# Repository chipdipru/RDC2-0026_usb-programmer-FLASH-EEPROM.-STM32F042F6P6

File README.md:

<p>USB-программатор предназначен для записи и чтения микросхем памяти серий 24хх, 25хх, 93хх, 95хх. На плате установлена панель для микросхем в корпусе DIP-8, предусмотрены посадочные места для микросхем в корпусах SOIC-8 и SOIC-16 (для серии 25хх). Все необходимые для работы с микросхемами сигналы выведены на разъемы.<br>
Для записи микросхем памяти необходимы файлы формата .bin. Программатор автоматически конвертирует файлы E2Prom.Hex SigmaStudio в .bin для записи.</p>
<p>Характеристики<br>
поддерживаемые серии микросхем памяти: 24хх, 25хх, 93хх, 95хх<br>
поддерживаемые корпуса: DIP-8, SOIC-8, SOIC-16 (для серии 25хх)<br>
максимальная тактовая частота: 24хх – 1 МГц; 25хх / 95хх – 24 МГц; 93хх – 2 МГц<br>
напряжение питания микросхем памяти: 3,3 В<br>
формат файла для записи / чтения: .bin, SigmaStudio .hex<br>
чтение / запись регистра состояния микросхем памяти<br>
хранение шаблонов микросхем памяти в формате .txt</p>

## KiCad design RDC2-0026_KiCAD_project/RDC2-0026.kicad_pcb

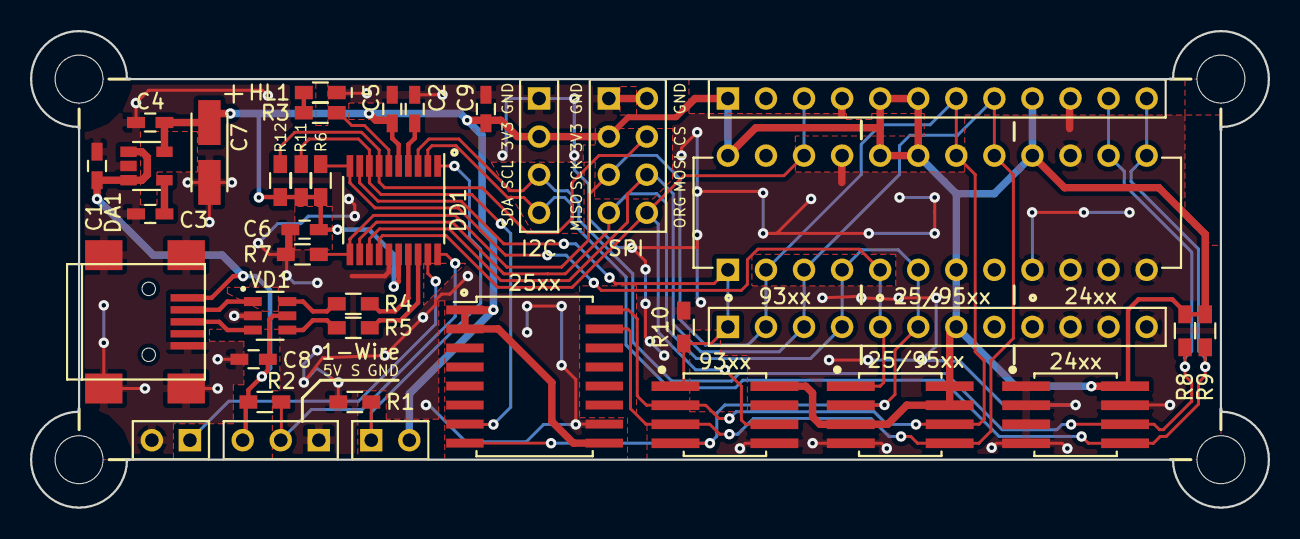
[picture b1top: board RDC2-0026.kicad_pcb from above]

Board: 2 copper layers, 82.6 x 31.8 mm, 38 parts (0 on the bottom side), 26 nets.

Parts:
24xx: 24XX EEPROM; SOIC-8_combo_Pitch1.27mm
25/95xx: 25LC_EEPROM; SOIC-8_combo_Pitch1.27mm
25xx: 25xx_spi_flash; SOIC-16_7.5x10.3mm_Pitch1.27mm_long_pads
93xx: 93LCxxC; SOIC-8_combo_Pitch1.27mm
C1, C4: 4,7мкФ; C_0603_HandSoldering
C2, C5, C6, C8, C9: 0,1мкФ; C_0603_HandSoldering
C3: 0,01мкФ; C_0603_HandSoldering
C7: 10мкФ; TantalC_SizeA_EIA-3216_HandSoldering_mm
DA1: LP2985AIM5-3.3; SOT-23-5_mm
DD1: STM32F042F6Px; TSSOP-20_4.4x6.5mm_Pitch0.65mm
HL1: LED; LED_0603_HandSoldering
R1, R6, R7, R10, R11, R12: 10k; R_0603_HandSoldering
R2: 4k7; R_0603_HandSoldering
R3: 300R; R_0603_HandSoldering
R4, R5: 22R; R_0603_HandSoldering
R8, R9: 3k3; R_0603_HandSoldering
VD1: USBLC6; SOT23-6L
XP1, XP4: PLS-2; Pin_Header_Straight_1x02_mm
XP3: CONN_01X04; Pin_Header_Straight_1x04_mm
XP5: CONN_02X04; Pin_Header_Straight_2x04_mm
XS1: USB_OTG; USB_Mini-B_mm
XS2: CONN_01X03; Pin_Header_Straight_1x03_mm
XS3, XS5: CONN_01X12; Pin_Header_Straight_1x12_mm
XS4: dip-24_IC; DIP-24_W7.62mm_0.9x1.5

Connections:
5V: C1.1, C8.1, DA1.1, DA1.3, R2.1, VD1.5, XS1.1, XS2.3
GND: 24xx.1, 24xx.2, 24xx.3, 24xx.4, 24xx.7, 25/95xx.4, 25xx.10, 93xx.5, C1.2, C2.2, C3.2, C4.2, C5.2, C6.2, C7.2, C8.2, C9.2, DA1.2, DD1.15, HL1.1, R1.2, R7.1, R10.2, VD1.2, XP3.1, XP4.2, XP5.1, XP5.2, XS1.5, XS1.6, XS2.1, XS3.8, XS3.9, XS3.10, XS3.11, XS3.12, XS4.8, XS4.9, XS4.10, XS4.11, XS4.12, XS4.15, XS4.21, XS5.4, XS5.10
unnamed: C3.1, DA1.4
unnamed: DD1.1, R1.1, XP1.1
unnamed: DD1.6, R3.1
unnamed: DD1.17, R4.1
unnamed: DD1.18, R5.1
unnamed: DD1.19, XP4.1
unnamed: HL1.2, R3.2
unnamed: VD1.1, XS1.2
unnamed: VD1.3, XS1.3
ORG: 93xx.6, DD1.14, XP5.8, XS4.22, XS5.3
RST: C2.1, DD1.4
SCL: 24xx.6, DD1.3, R8.2, XP3.3, XS4.14, XS5.11
SDA: 24xx.5, DD1.2, R9.2, XP3.4, XS4.13, XS5.12
SPI_MISO: 25/95xx.2, 25xx.8, 93xx.4, DD1.12, XP5.7, XS3.4, XS3.6, XS4.4, XS4.6
SPI_MOSI: 25/95xx.5, 25xx.15, 93xx.3, DD1.13, XP5.6, XS3.3, XS4.3, XS4.17, XS5.8
SPI_NSS1: 25/95xx.1, DD1.10, R6.1, XS3.5, XS4.5
SPI_NSS2: 93xx.1, DD1.9, R10.1, XS3.1, XS4.1
SPI_NSS3: 25xx.7, DD1.8, R11.1
SPI_NSS4: DD1.7, R12.2, XP5.4
SPI_SCK: 25/95xx.6, 25xx.16, 93xx.2, DD1.11, R7.2, XP5.5, XS3.2, XS4.2, XS4.18, XS5.7
SWCLK/1_WIRE: DD1.20, R2.2, XS2.2
USB_DM: R4.2, VD1.6
USB_DP: R5.2, VD1.4
VDD: 24xx.8, 25/95xx.3, 25/95xx.7, 25/95xx.8, 25xx.1, 25xx.2, 25xx.9, 93xx.8, C4.1, C5.1, C6.1, C7.1, C9.1, DA1.5, DD1.5, DD1.16, R6.2, R8.1, R9.1, R11.2, R12.1, XP1.2, XP3.2, XP5.3, XS3.7, XS4.7, XS4.16, XS4.19, XS4.20, XS4.24, XS5.1, XS5.5, XS5.6, XS5.9

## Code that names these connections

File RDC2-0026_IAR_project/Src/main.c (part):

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  RCC->I2C_TIMER_ENR &= ~I2C_TIMER_CLK_EN;
    
  //SPI
  SPI_GPIO->OSPEEDR |= (1 << (2 * SPI_SCK_PIN)) | (1 << (2 * SPI_MISO_PIN)) | (1 << (2 * SPI_MOSI_PIN));
  RCC->APB2ENR |= RCC_APB2ENR_SPI1EN;
  SPI_PORT->CR1 = SPI_CR1_MSTR | SPI_CR1_SSI | SPI_CR1_SSM;
  SPI_PORT->CR2 = SPI_CR2_FRXTH | SPI_CR2_DS_2 | SPI_CR2_DS_1 | SPI_CR2_DS_0;
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
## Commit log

2018-09-18 USB программатор FLASH и EEPROM. STM32F042F6P6
2018-09-18 Soft для программирования
    SigmaStudio compatible
2018-09-18 небольшая база микросхем памяти
2018-09-18 visual studio project
2018-09-18 Kicad проект платы RDC2-0026
2018-09-18 IAR project
2018-09-18 schematic
2018-09-18 Руководство пользователя
2018-12-26 Win XP soft

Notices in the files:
RDC2-0026_IAR_project/Src/main.c:
COPYRIGHT(c) ЗАО «ЧИП и ДИП», 2017
